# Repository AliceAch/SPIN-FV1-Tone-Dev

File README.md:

# SPIN FV1 Tone Dev

A PCB Tone Development board for Guitar Effects, built around the SPIN FV1 DSP IC. There's not much so far... Look at Docs if you want to look at the project without opening it in KiCad.

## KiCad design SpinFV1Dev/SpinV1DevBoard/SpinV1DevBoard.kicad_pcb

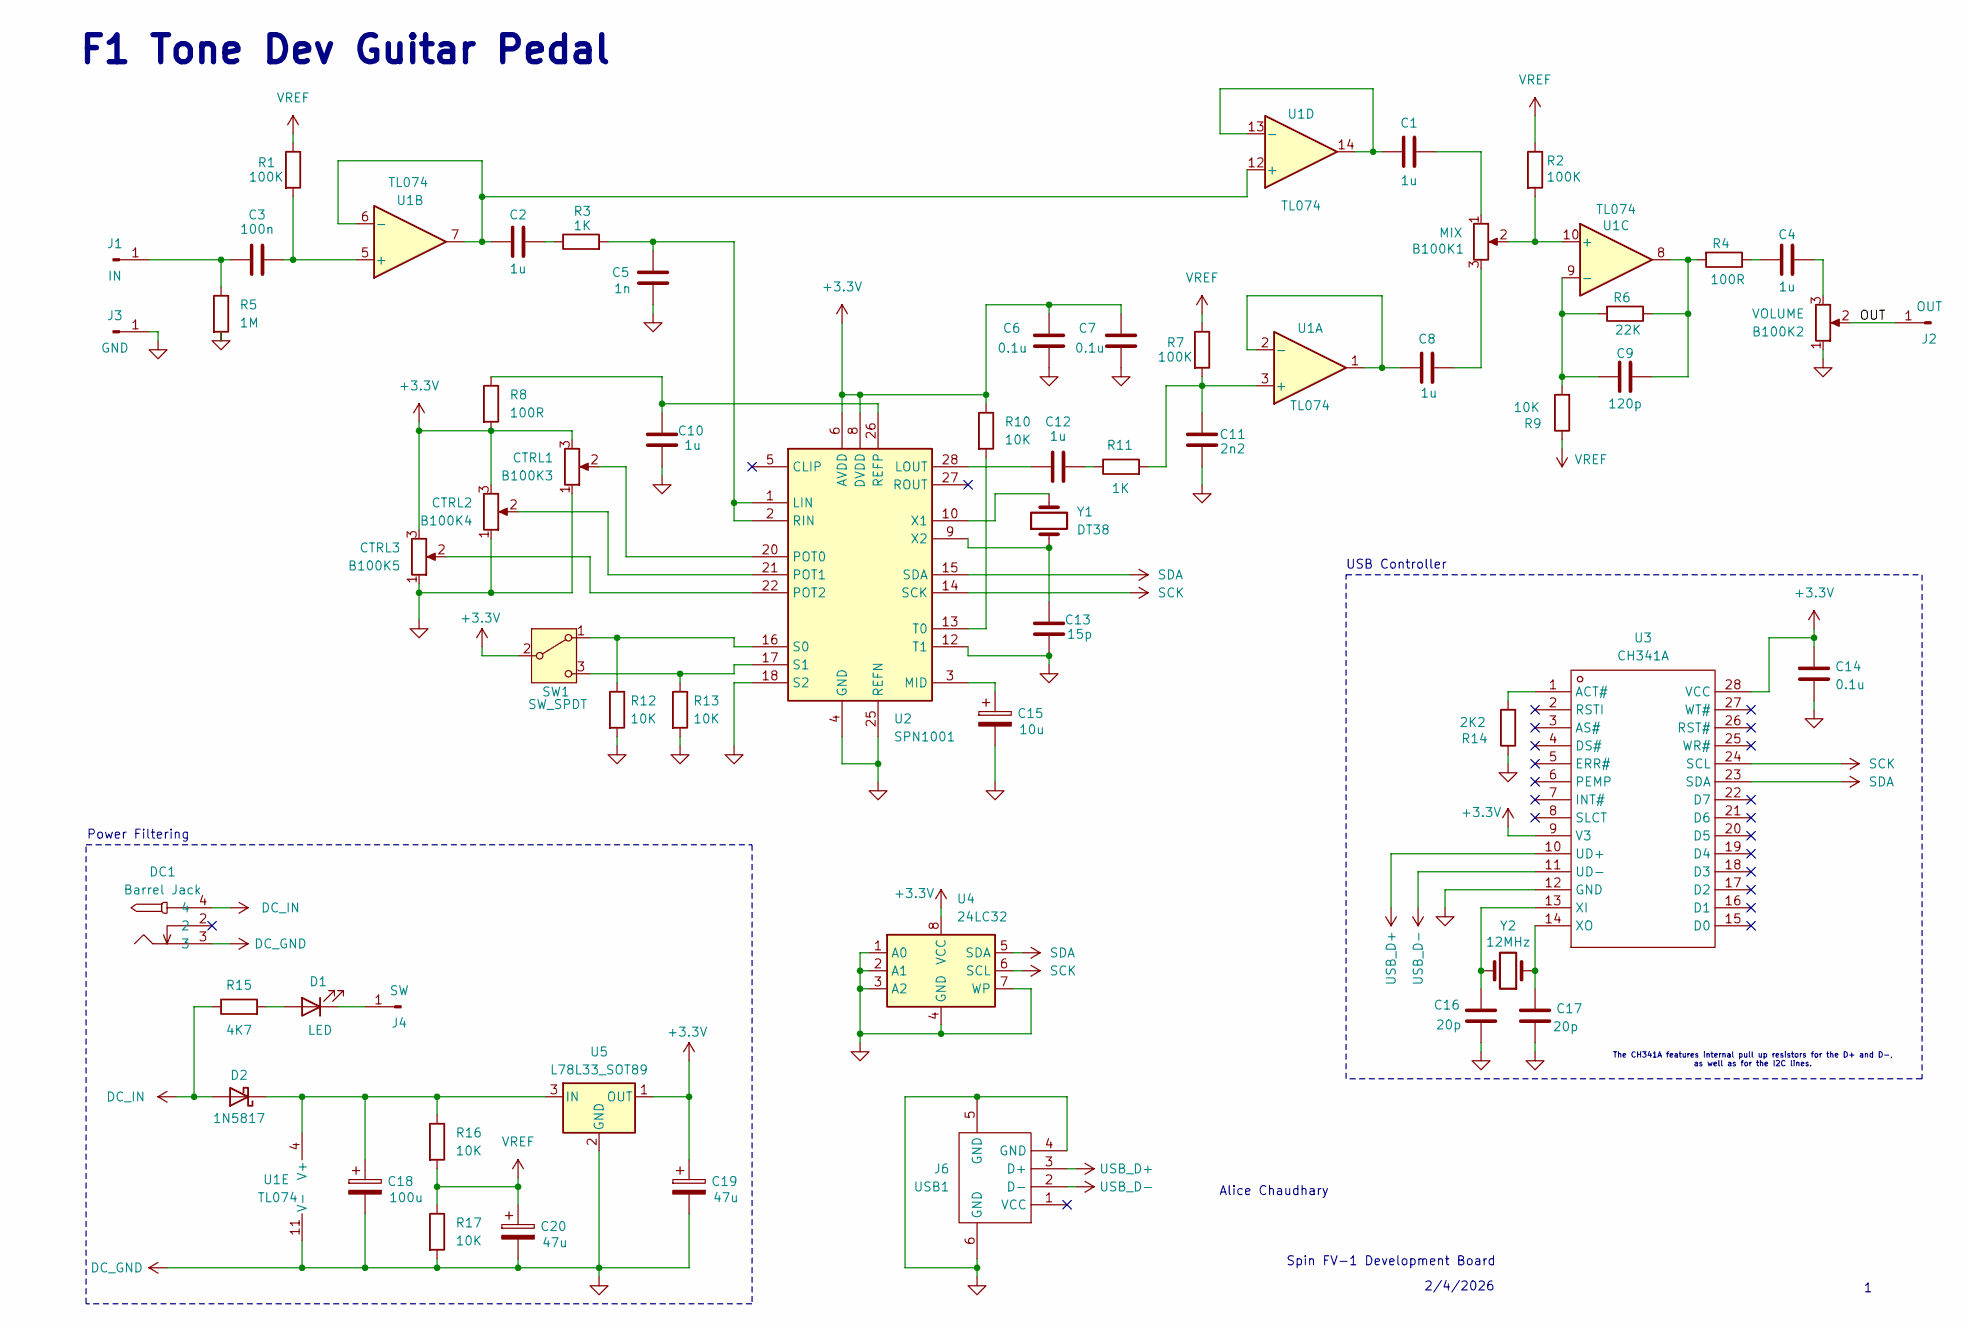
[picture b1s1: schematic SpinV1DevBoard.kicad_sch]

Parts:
B100K1: MIX; Potentiometer_Modified
B100K2: VOLUME; Potentiometer_Modified
B100K3: CTRL1; Potentiometer_Modified
B100K4: CTRL2; Potentiometer_Modified
B100K5: CTRL3; Potentiometer_Modified
C1, C2, C4, C8, C10, C12: 1u; C_0805_2012Metric
C3: 100n; C_0805_2012Metric
C5: 1n; C_0805_2012Metric
C6, C7, C14: 0.1u; C_0805_2012Metric
C9: 120p; C_0805_2012Metric
C11: 2n2; C_0805_2012Metric
C13: 15p; C_0805_2012Metric
C15: 10u; C_0805_2012Metric
C16, C17: 20p; C_0805_2012Metric
C18: 100u; CP_Radial_D5.0mm_P2.50mm
C19, C20: 47u; CP_Radial_D5.0mm_P2.50mm
D1: LED; LED_D5.0mm
D2: 1N5817; D_DO-41_SOD81_P5.08mm_Vertical_AnodeUp
DC1: Barrel Jack; DC-IN-TH_DC-005-5.5-2.0
J1: IN; SolderWire-1.5sqmm_1x01_D1.7mm_OD3.9mm
J2: OUT; SolderWire-1.5sqmm_1x01_D1.7mm_OD3.9mm
J3: GND; SolderWire-1.5sqmm_1x01_D1.7mm_OD3.9mm
J4: SW; SolderWire-1.5sqmm_1x01_D1.7mm_OD3.9mm
R1, R2, R7: 100K; R_0805_2012Metric
R3, R11: 1K; R_0805_2012Metric
R4, R8: 100R; R_0805_2012Metric
R5: 1M; R_0805_2012Metric
R6: 22K; R_0805_2012Metric
R9, R10, R12, R13, R16, R17: 10K; R_0805_2012Metric
R14: 2K2; R_0805_2012Metric
R15: 4K7; R_0805_2012Metric
SW1: SW_SPDT; SW-TH_K3-SPDT
U1: TL074
U2: SPN1001; SOIC-28W_7.5x17.9mm_P1.27mm
U3: CH341A; Manufacturer Part CH341A; LCSC Part Name CH341A
U4: 24LC32
U5: L78L33_SOT89; SOT-89-3
USB1: J6; USB-A-TH_USB-302-T
Y1: DT38
Y2: 12MHz

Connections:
+3.3V: B100K3.3, B100K4.3, B100K5.3, C6.1, C7.1, C14.2, C19.1, R8.2, R10.1, SW1.2 (B), U2.6 (AVDD), U2.8 (DVDD), U2.23 (DVDD), U3.9 (V3), U3.28 (VCC), U4.8 (VCC), U5.1 (OUT)
/OUT: B100K2.2, J2.1
DC_GND: B100K2.1, B100K3.1, B100K4.1, B100K5.1, C5.1, C6.2, C7.2, C10.2, C11.1, C13.2, C14.1, C15.2, C16.1, C17.1, C18.2, C19.2, C20.2, DC1.3, J3.1, R5.2, R12.2, R13.2, R14.1, R17.2, U1.11 (V-), U2.4 (GND), U2.7 (GND), U2.11 (GND), U2.12 (T1), U2.18 (S2), U2.19 (GND), U2.24 (GND), U2.25 (REFN), U3.12 (GND), U4.1 (A0), U4.2 (A1), U4.3 (A2), U4.4 (GND), U4.7 (WP), U5.2 (GND), USB1.4 (GND), USB1.5 (GND), USB1.6 (GND)
DC_IN: D2.2 (A), DC1.4, R15.1
unnamed: B100K1.1, C1.2
unnamed: B100K1.3, C8.2
unnamed: B100K2.3, C4.2
unnamed: C2.2, R3.1
unnamed: C4.1, R4.1
unnamed: C9.2, R4.2, R6.1, U1.8
unnamed: C12.2, R11.1
unnamed: D1.2 (A), R15.2
unnamed: D1.1 (K), J4.1
unnamed: C18.1, D2.1 (K), R16.1, U1.4 (V+), U5.3 (IN)
unnamed: C3.1, J1.1, R5.1
unnamed: R12.1, SW1.1 (A), U2.16 (S0)
unnamed: R13.1, SW1.3 (C), U2.17 (S1)
unnamed: C11.2, R7.2, R11.2, U1.3 (+)
unnamed: C8.1, U1.1, U1.2 (-)
unnamed: C3.2, R1.2, U1.5 (+)
unnamed: C2.1, U1.6 (-), U1.7, U1.12 (+)
unnamed: B100K1.2, R2.2, U1.10 (+)
unnamed: C9.1, R6.2, R9.2, U1.9 (-)
unnamed: C1.1, U1.13 (-), U1.14
unnamed: C5.2, R3.2, U2.1 (LIN), U2.2 (RIN)
unnamed: C12.1, U2.28 (LOUT)
unnamed: C15.1, U2.3 (MID)
unnamed: B100K3.2, U2.20 (POT0)
unnamed: B100K4.2, U2.21 (POT1)
unnamed: B100K5.2, U2.22 (POT2)
unnamed: C10.1, R8.1, U2.26 (REFP)
unnamed: R10.2, U2.13 (T0)
unnamed: U2.10 (X1), Y1.2
unnamed: C13.1, U2.9 (X2), Y1.1
unnamed: R14.2, U3.1 (ACT#)
unnamed: C16.2, U3.13 (XI), Y2.2
unnamed: C17.2, U3.14 (XO), Y2.1
SCK: U2.14 (SCK), U3.24 (SCL), U4.6 (SCL)
SDA: U2.15 (SDA), U3.23 (SDA), U4.5 (SDA)
USB_D+: U3.10 (UD+), USB1.3 (D+)
USB_D-: U3.11 (UD-), USB1.2 (D-)
VREF: C20.1, R1.1, R2.1, R7.1, R9.1, R16.2, R17.1

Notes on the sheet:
The CH341A features internal pull up resistors for the D+ and D-, as well as for the I2C lines.
F1 Tone Dev Guitar Pedal
2/4/2026
Alice Chaudhary
Spin FV-1 Development Board
Power Filtering
USB Controller

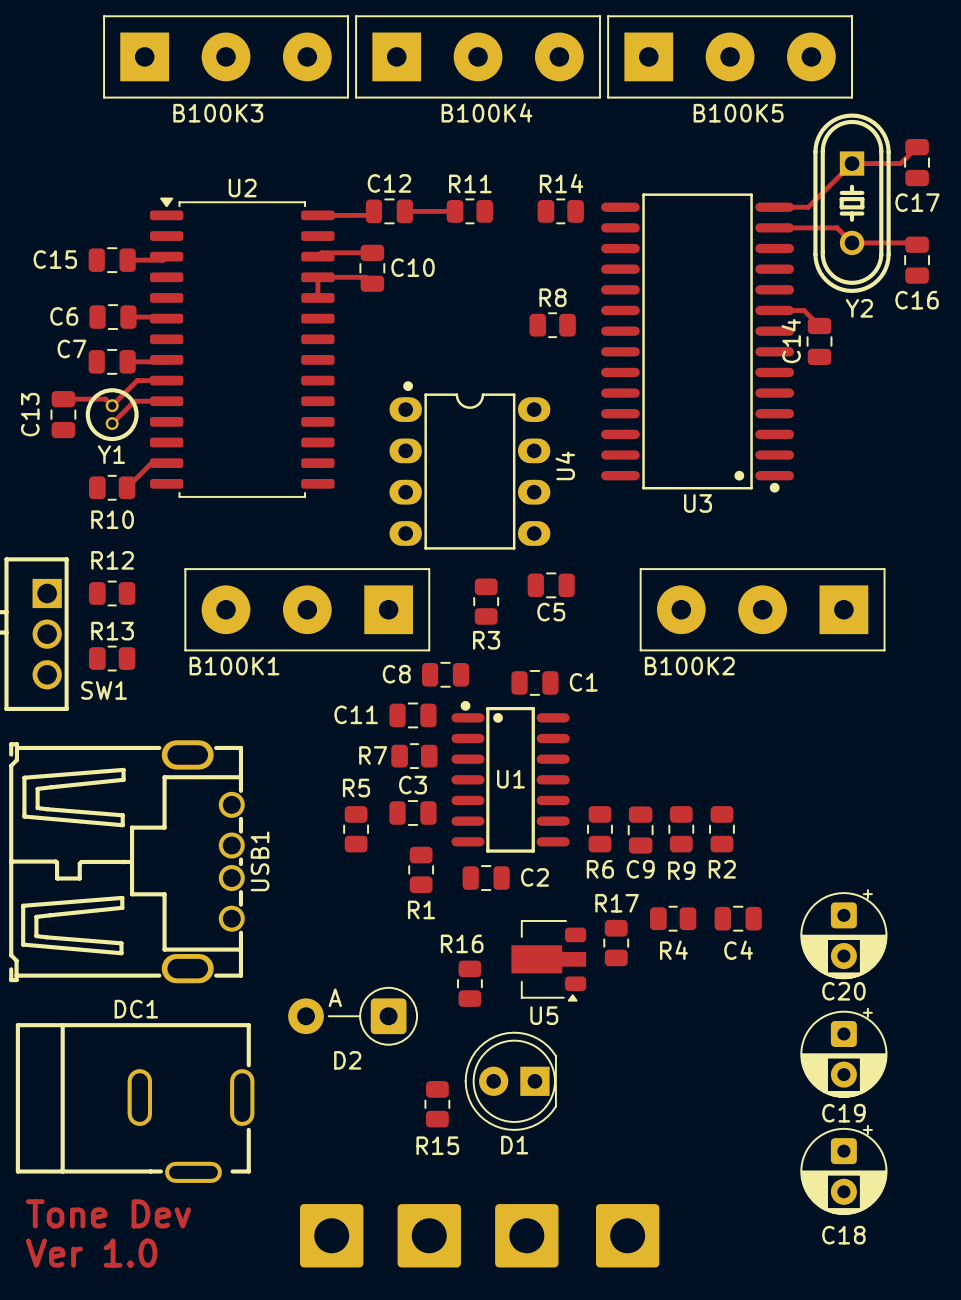
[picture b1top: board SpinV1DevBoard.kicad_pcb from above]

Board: 2 copper layers, 58 parts (0 on the bottom side), 42 nets.
